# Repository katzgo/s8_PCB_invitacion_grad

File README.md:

# s8_PCB_invitacion_grad
Invitación para la graduación de las carreras IE/IRS/IMD

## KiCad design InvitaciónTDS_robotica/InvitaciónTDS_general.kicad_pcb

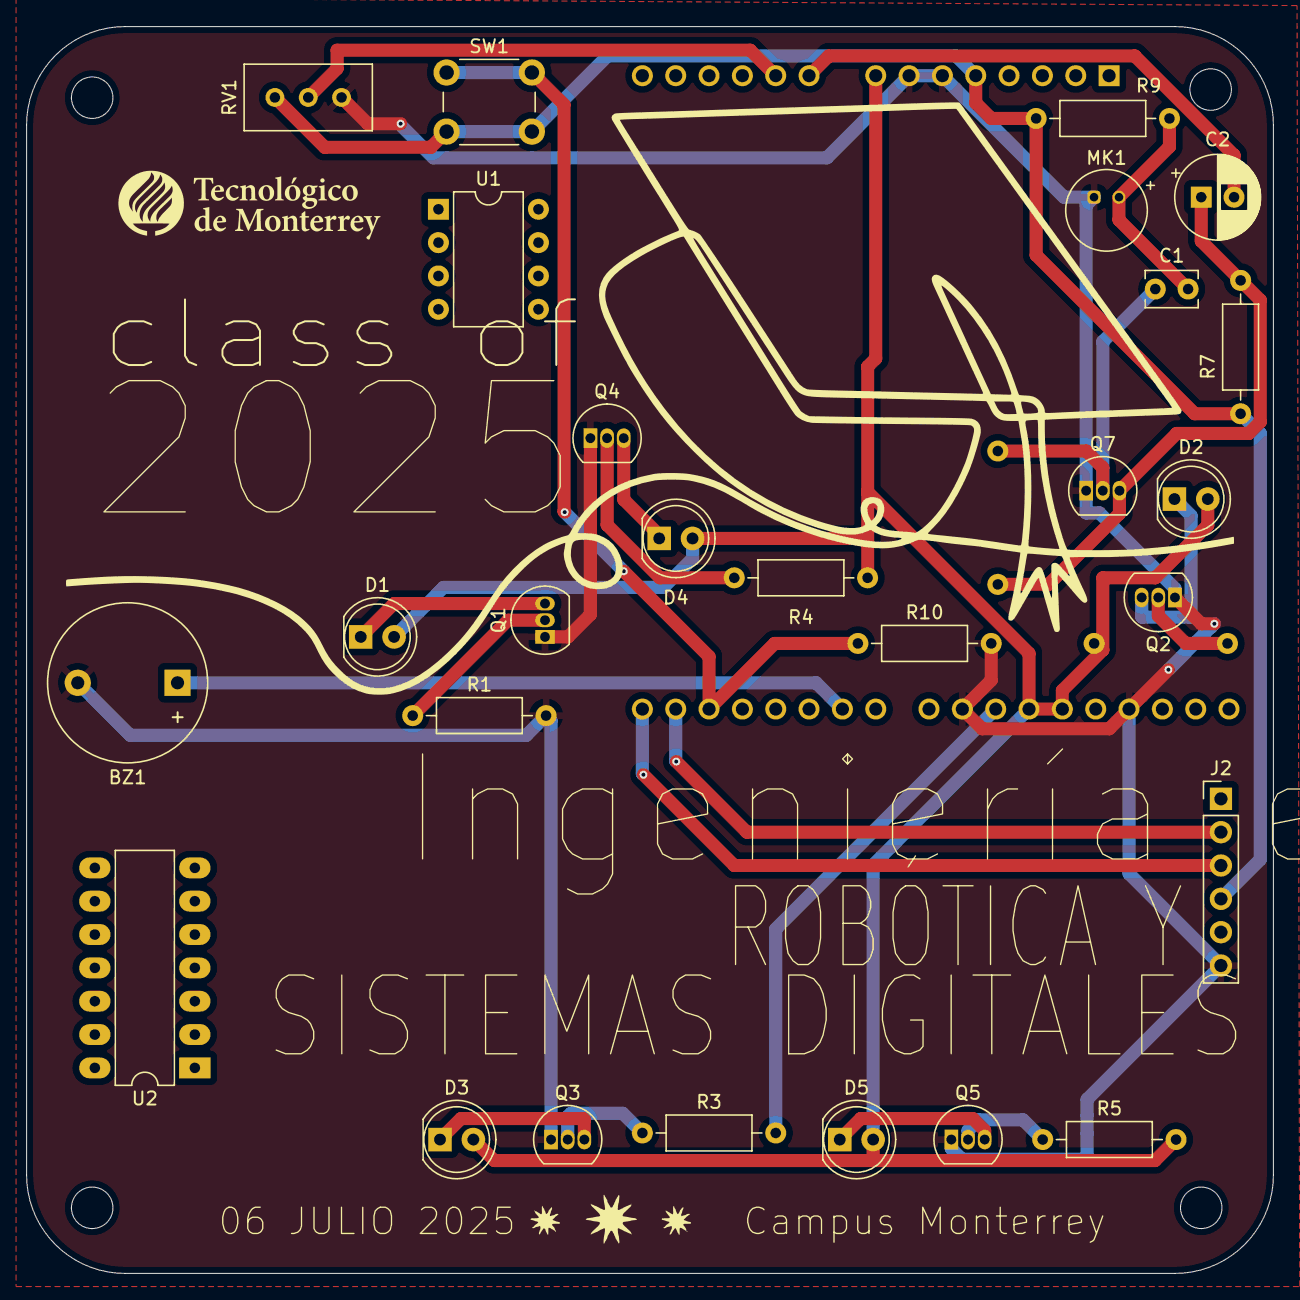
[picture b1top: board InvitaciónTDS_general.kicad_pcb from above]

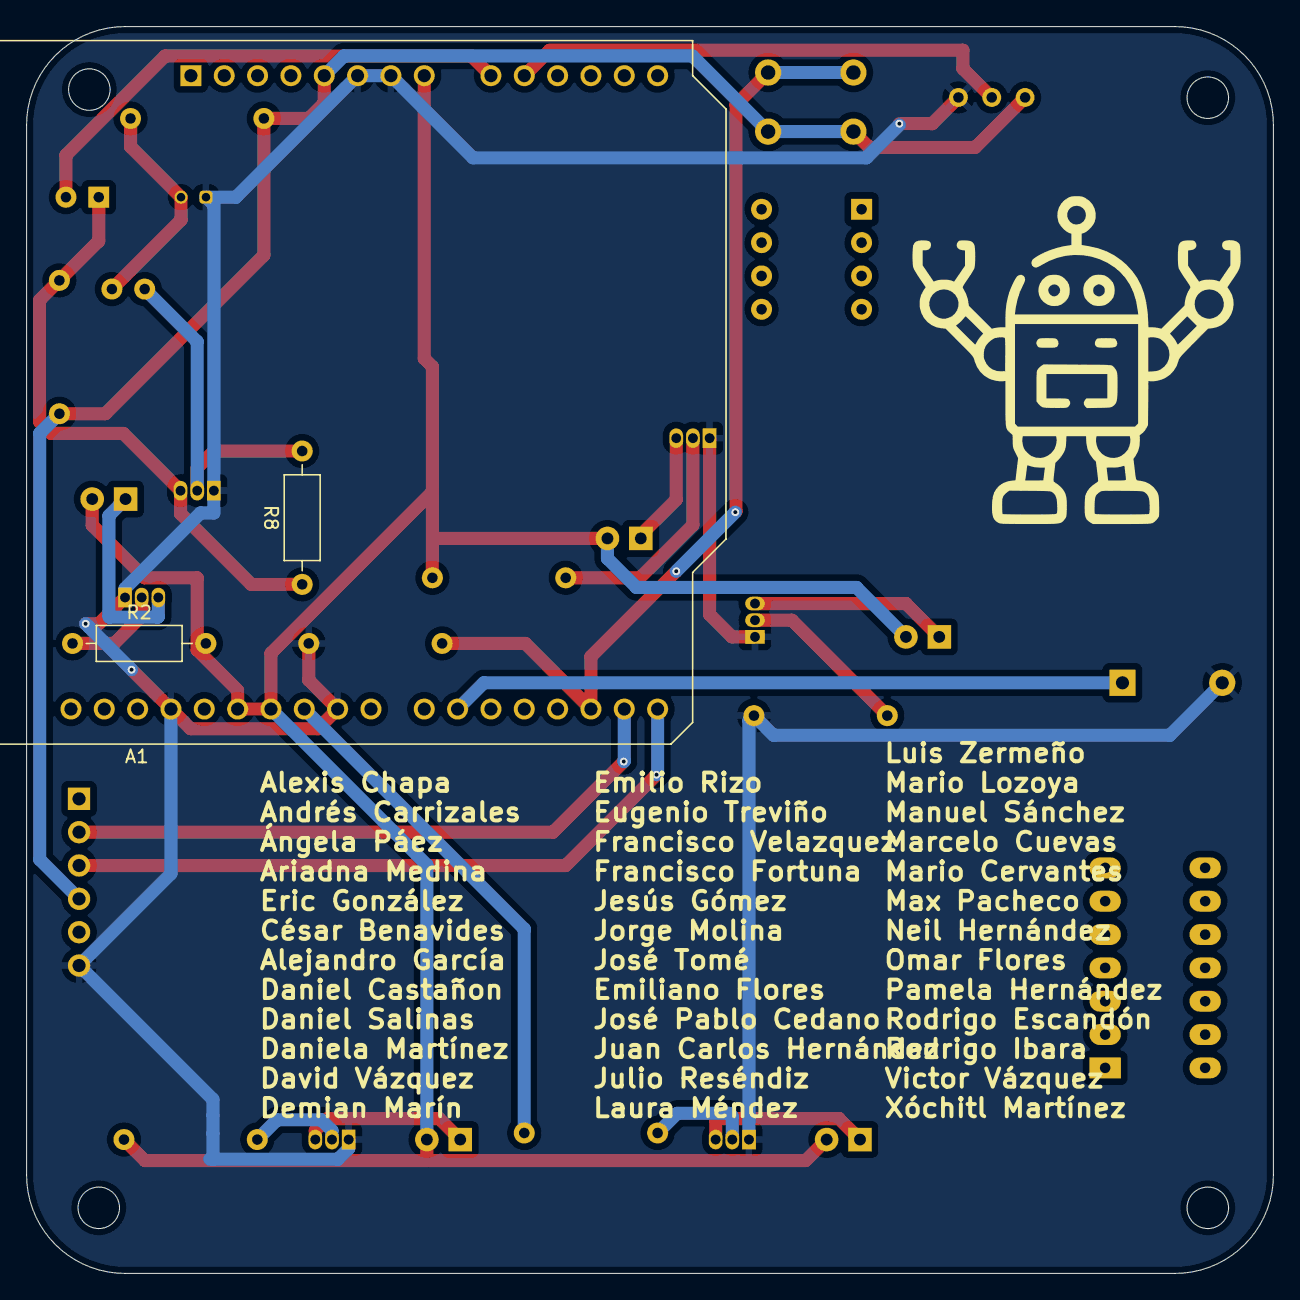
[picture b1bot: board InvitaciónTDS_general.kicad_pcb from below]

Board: 2 copper layers, 95.0 x 95.0 mm, 30 parts (3 on the bottom side), 23 nets.

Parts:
A1: Arduino_UNO_R3
BZ1: Buzzer; Buzzer_12x9.5RM7.6
C1: C_ceramico; C_Disc_D3.8mm_W2.6mm_P2.50mm
C2: C_Polarized; CP_Radial_D6.3mm_P2.50mm
D1, D2, D3, D4, D5: LED; LED_D5.0mm
J2: FTDI Connector; PinHeader_1x06_P2.54mm_Vertical
MK1: Microphone; POM-2244P-C3310-2-R
Q1, Q2, Q3, Q4, Q5, Q7: 2N2219; TO-92_Inline
R1, R2, R3, R4, R5, R7, R8, R9, R10: R; R_Axial_DIN0207_L6.3mm_D2.5mm_P10.16mm_Horizontal
RV1: R_Potentiometer; Potentiometer_Bourns_3386C_Horizontal
SW1: SW_Push; SW_PUSH_6mm
U1: LM358; DIP-8_W7.62mm
U2: 74LS08; DIP-14_W7.62mm_LongPads

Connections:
/LEDSchem2/PinName: A1.25 (D10), R3.2
/LEDSchem/PinName: A1.8 (VIN), A1.23 (D8), A1.26 (D11), A1.27 (D12), D1.2 (A), D2.2 (A), D3.2 (A), D4.2 (A), D5.2 (A), R2.2, R4.2, R5.2
GND: A1.6 (GND), A1.7 (GND), A1.24 (D9), A1.29 (GND), BZ1.2 (-), J2.6, MK1.1 (-), Q1.1 (E), Q2.1 (E), Q3.1 (E), Q4.1 (E), Q5.1 (E), Q7.1 (E), R1.2, R10.2, RV1.3
unnamed: A1.5 (+5V), J2.4, R7.1, R9.1, RV1.1, SW1.2
unnamed: A1.9 (A0), C2.2
unnamed: A1.10 (A1), RV1.2
unnamed: A1.15 (D0/RX), J2.3
unnamed: A1.16 (D1/TX), J2.2
unnamed: A1.17 (D2), R10.1, SW1.1
unnamed: A1.21 (D6), BZ1.1 (+)
unnamed: D1.1 (K), Q1.3 (C)
unnamed: D2.1 (K), Q2.3 (C)
unnamed: D3.1 (K), Q3.3 (C)
unnamed: D4.1 (K), Q4.3 (C)
unnamed: D5.1 (K), Q5.3 (C)
unnamed: C1.2, MK1.2 (+), R9.2
unnamed: Q1.2 (B), R1.1
unnamed: Q2.2 (B), R2.1
unnamed: Q3.2 (B), R3.1
unnamed: Q4.2 (B), R4.1
unnamed: Q5.2 (B), R5.1
unnamed: C1.1, Q7.2 (B), R8.2
unnamed: C2.1, Q7.3 (C), R7.2, R8.1

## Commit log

2025-02-23 Primer draft invitación general
2025-02-24 Adición de gráficos frente PCB general
2025-03-10 Esquemático actualizado, rev 1, pre-retro
2025-03-10 Copias para cada carrera del general, cambio en footprint transistor
2025-03-19 Acomodo componentes Layout Electronica
2025-03-19 update robotica
2025-03-19 PCB version 1 electronica
2025-03-21 terminado
2025-03-21 terminado con algunos warnings
2025-03-24 Added Electronica Production folders
